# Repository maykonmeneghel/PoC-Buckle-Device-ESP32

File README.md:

## Welcome to GitHub Pages

You can use the [editor on GitHub](https://github.com/maykonmeneghel/buckledevice/edit/master/README.md) to maintain and preview the content for your website in Markdown files.

Whenever you commit to this repository, GitHub Pages will run [Jekyll](https://jekyllrb.com/) to rebuild the pages in your site, from the content in your Markdown files.

### Markdown

Markdown is a lightweight and easy-to-use syntax for styling your writing. It includes conventions for

```markdown
Syntax highlighted code block

# Header 1
## Header 2
### Header 3

- Bulleted
- List

1. Numbered
2. List

**Bold** and _Italic_ and `Code` text

[Link](url) and 
```

For more details see [GitHub Flavored Markdown](https://guides.github.com/features/mastering-markdown/).

### Jekyll Themes

Your Pages site will use the layout and styles from the Jekyll theme you have selected in your [repository settings](https://github.com/maykonmeneghel/buckledevice/settings). The name of this theme is saved in the Jekyll `_config.yml` configuration file.

### Support or Contact

Having trouble with Pages? Check out our [documentation](https://help.github.com/categories/github-pages-basics/) or [contact support](https://github.com/contact) and we’ll help you sort it out.

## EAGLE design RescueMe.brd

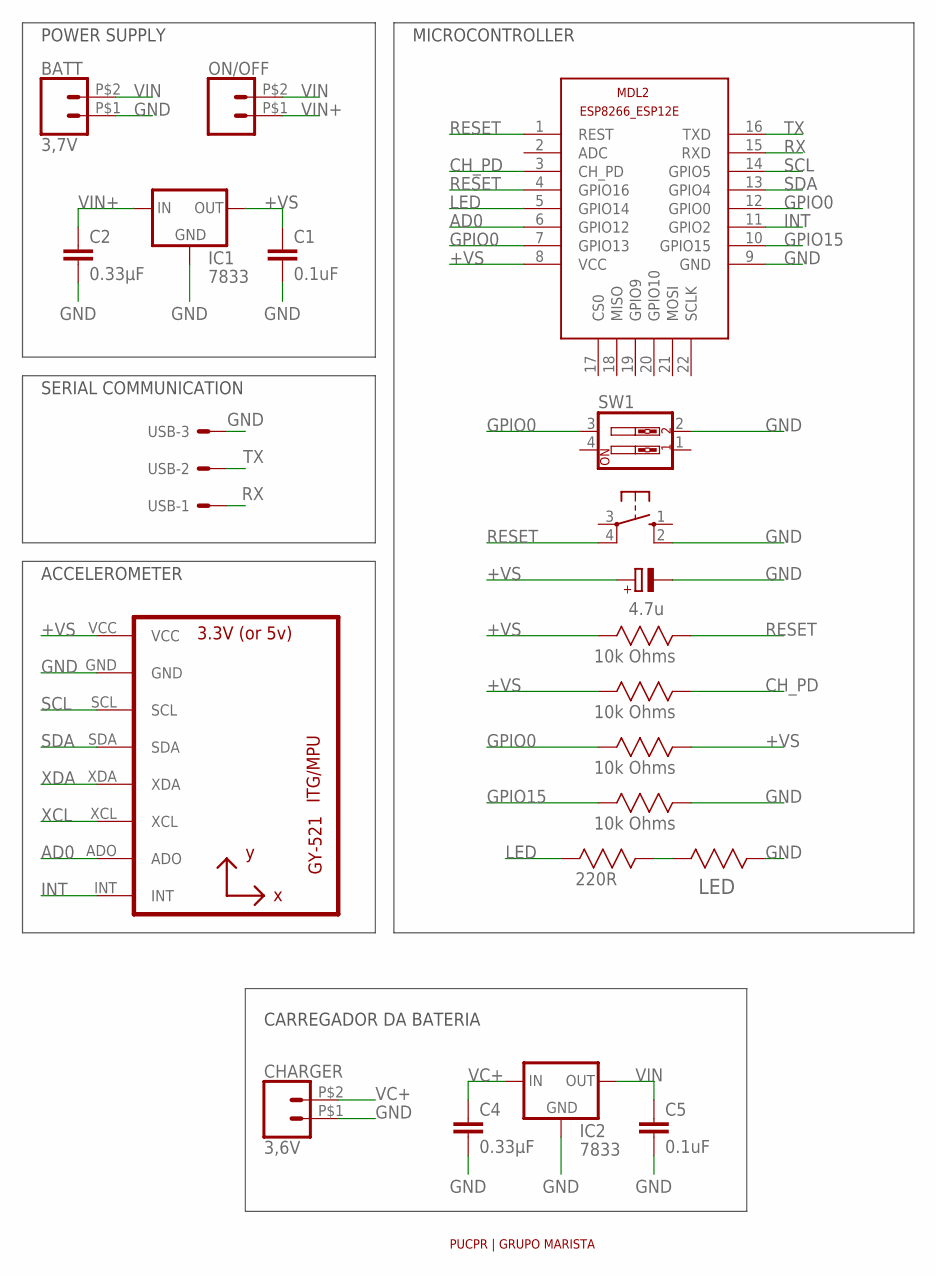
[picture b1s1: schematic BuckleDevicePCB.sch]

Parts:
BATT: 3,7V; 1X02_BIG
C1, C5: 0.1uF; 0805
C2, C4: 0.33µF; 0805
C7: 4.7u; 153CLV-0405
CHARGER: 3,6V; 1X02_BIG
IC1, IC2: 7833; 78XXS
LED: ERA-6AEB221V; RESC2013X65N
MDL2: ESP8266; ESP8266-ESP12E
ON/OFF: CONN_02PTH2; 1X02_BIG
R_CHPD: 10k Ohms; RESC2013X65N
R_G0, R_G15: 10k Ohms; RESC2013X65N
R_LED: 220R; RESC2013X65N
R_RST: 10k Ohms; RESC2013X65N
S1: 10-XX; B3F-10XX
SW1: SW_DIP-2; DIPSWITCH-02
U1: GY-521MPU6050; GY-521
U$1: PUCPR_G; PUCPR
USB: 22-27-2031-03; 6410-03

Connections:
+VS: C1.1, C7.+, IC1.OUT, MDL2.8 (VCC), R_CHPD.2 (R2), R_G0.1 (R1), R_RST.2 (R2), U1.VCC
AD0: MDL2.6 (GPIO12), U1.ADO
CH_PD: MDL2.3 (CH_PD), R_CHPD.1 (R1)
GND: BATT.P$1 (1), C1.2, C2.2, C4.2, C5.2, C7.-, CHARGER.P$1 (1), IC1.GND, IC2.GND, LED.1 (R1), MDL2.9 (GND), R_G15.1 (R1), S1.2 (S1), SW1.2, U1.GND, USB.3
GPIO0: MDL2.7 (GPIO13), MDL2.12 (GPIO0), R_G0.2 (R2), SW1.3
GPIO15: MDL2.10 (GPIO15), R_G15.2 (R2)
INT: MDL2.11 (GPIO2), U1.INT
LED: MDL2.5 (GPIO14), R_LED.2 (R2)
unnamed: LED.2 (R2), R_LED.1 (R1)
RESET: MDL2.1 (REST), MDL2.4 (GPIO16), R_RST.1 (R1), S1.4 (P1)
RX: MDL2.15 (RXD), USB.1
SCL: MDL2.14 (GPIO5), U1.SCL
SDA: MDL2.13 (GPIO4), U1.SDA
TX: MDL2.16 (TXD), USB.2
VC+: C4.1, CHARGER.P$2 (2), IC2.IN
VIN: BATT.P$2 (2), C5.1, IC2.OUT, ON/OFF.P$2 (2)
VIN+: C2.1, IC1.IN, ON/OFF.P$1 (1)
XCL: U1.XCL
XDA: U1.XDA

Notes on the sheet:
CARREGADOR DA BATERIA
POWER SUPPLY
ACCELEROMETER
MICROCONTROLLER
SERIAL COMMUNICATION

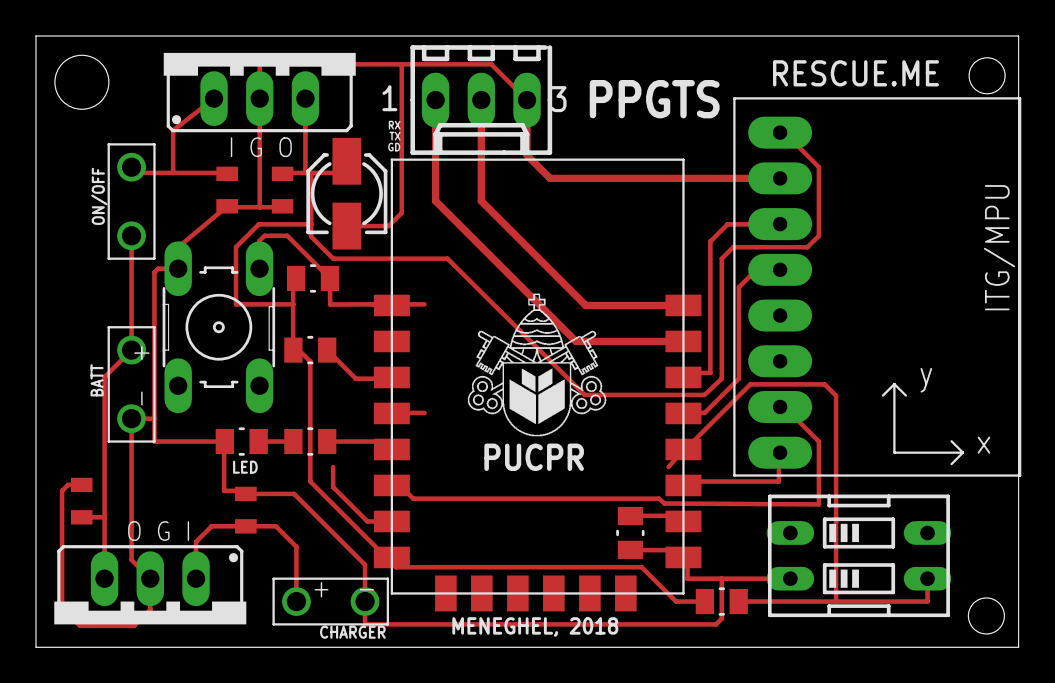
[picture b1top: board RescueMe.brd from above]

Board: 2 copper layers, 54.6 x 34.0 mm, 22 parts (0 on the bottom side), 17 nets.

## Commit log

2018-10-02 Set theme jekyll-theme-hacker
2018-10-02 Set theme jekyll-theme-cayman
2018-10-02 Rename RescueMe.sch to BuckleDevicePCB.sch
2018-10-02 Rename RescueMe.brd to BuckleDevicePCB.brd

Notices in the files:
parts and their libraries:
SparkFun: Licensing: CC v3.0 Share-Alike You are welcome to use this library for commercial purposes.
Capacitores: Licensing: Creative Commons ShareAlike 4.0 International - https://creativecommons.org/licenses/by-sa/4.0
